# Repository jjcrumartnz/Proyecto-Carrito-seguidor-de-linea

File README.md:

# Proyecto-Carrito-seguidor-de-linea

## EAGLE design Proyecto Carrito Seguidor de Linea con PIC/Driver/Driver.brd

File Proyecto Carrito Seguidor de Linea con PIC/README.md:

# Esquematicos-y-pogramacion-de-robot-seguidor-de-linea

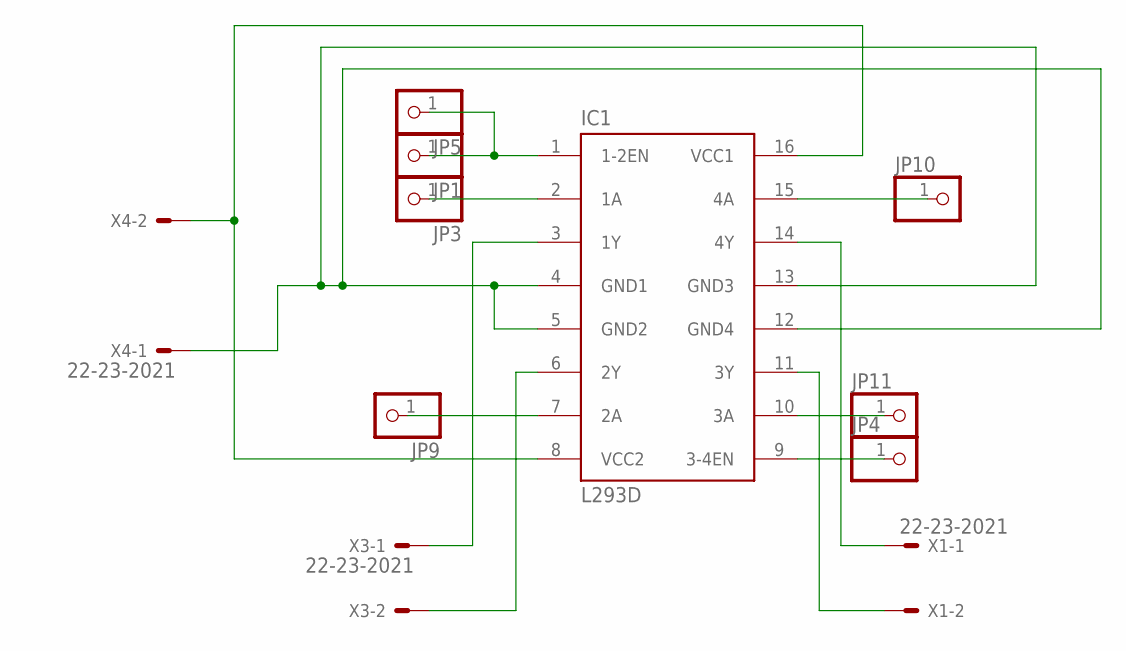
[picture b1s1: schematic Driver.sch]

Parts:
IC1: L293D; DIL16
JP1, JP3, JP4, JP5, JP9, JP10, JP11: PINHD-1X1; 1X01
X1, X3, X4: 22-23-2021

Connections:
unnamed: IC1.14 (4Y), X1.1
unnamed: IC1.1 (1-2EN), JP1.1, JP5.1
unnamed: IC1.2 (1A), JP3.1
unnamed: IC1.7 (2A), JP9.1
unnamed: IC1.10 (3A), JP11.1
unnamed: IC1.11 (3Y), X1.2
unnamed: IC1.3 (1Y), X3.1
unnamed: IC1.6 (2Y), X3.2
unnamed: IC1.15 (4A), JP10.1
unnamed: IC1.4 (GND1), IC1.5 (GND2), IC1.12 (GND4), IC1.13 (GND3), X4.1
unnamed: IC1.8 (VCC2), IC1.16 (VCC1), X4.2
unnamed: IC1.9 (3-4EN), JP4.1

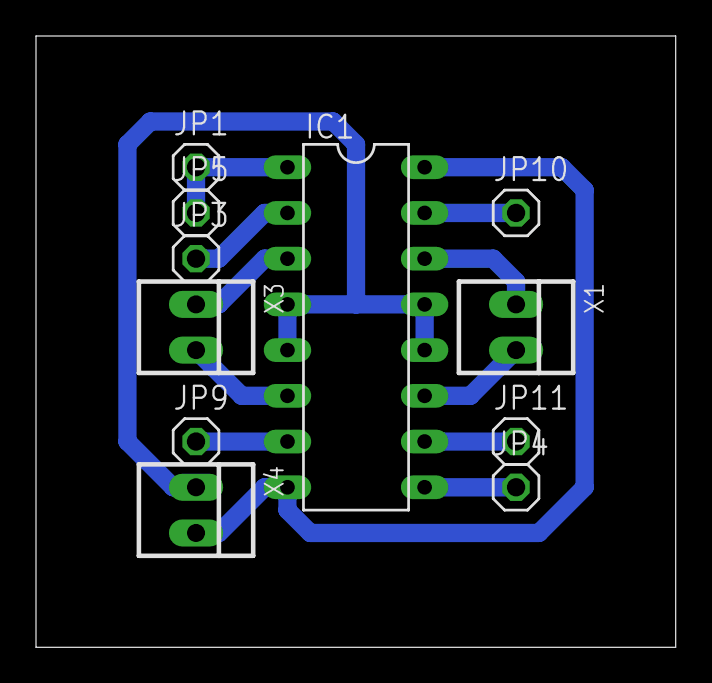
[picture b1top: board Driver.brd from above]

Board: 2 copper layers, 35.5 x 34.0 mm, 11 parts (0 on the bottom side), 12 nets.

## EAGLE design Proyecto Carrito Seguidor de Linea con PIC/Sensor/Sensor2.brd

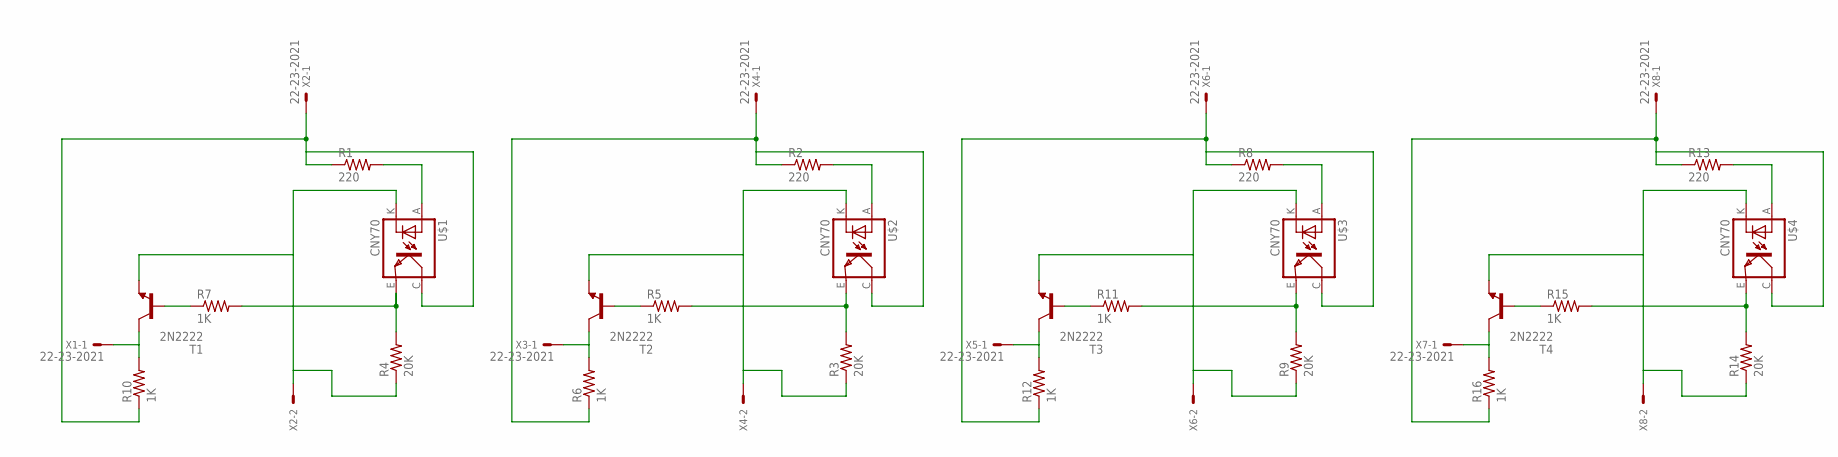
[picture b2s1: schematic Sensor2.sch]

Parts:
R1, R2, R8, R13: 220; 0204/7
R3, R4, R9, R14: 20K; 0204/7
R5, R6, R7, R10, R11, R12, R15, R16: 1K; 0204/7
T1, T2, T3, T4: 2N2222; TO18
U$1, U$2, U$3, U$4: CNY70; 4
X1, X2, X3, X4, X5, X6, X7, X8: 22-23-2021

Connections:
unnamed: R1.2, U$1.A
unnamed: R4.1, T1.1 (E), U$1.K (C), X2.2
unnamed: R2.2, U$2.A
unnamed: R3.1, T2.1 (E), U$2.K (C), X4.2
unnamed: R4.2, R7.2, U$1.E (EMI)
unnamed: R3.2, R5.2, U$2.E (EMI)
unnamed: R10.2, T1.3 (C), X1.1
unnamed: R7.1, T1.2 (B)
unnamed: R6.2, T2.3 (C), X3.1
unnamed: R1.1, R10.1, U$1.C (COL), X2.1
unnamed: R5.1, T2.2 (B)
unnamed: R2.1, R6.1, U$2.C (COL), X4.1
unnamed: R8.2, U$3.A
unnamed: R9.1, T3.1 (E), U$3.K (C), X6.2
unnamed: R9.2, R11.2, U$3.E (EMI)
unnamed: R12.2, T3.3 (C), X5.1
unnamed: R11.1, T3.2 (B)
unnamed: R8.1, R12.1, U$3.C (COL), X6.1
unnamed: R13.2, U$4.A
unnamed: R14.1, T4.1 (E), U$4.K (C), X8.2
unnamed: R14.2, R15.2, U$4.E (EMI)
unnamed: R16.2, T4.3 (C), X7.1
unnamed: R15.1, T4.2 (B)
unnamed: R13.1, R16.1, U$4.C (COL), X8.1

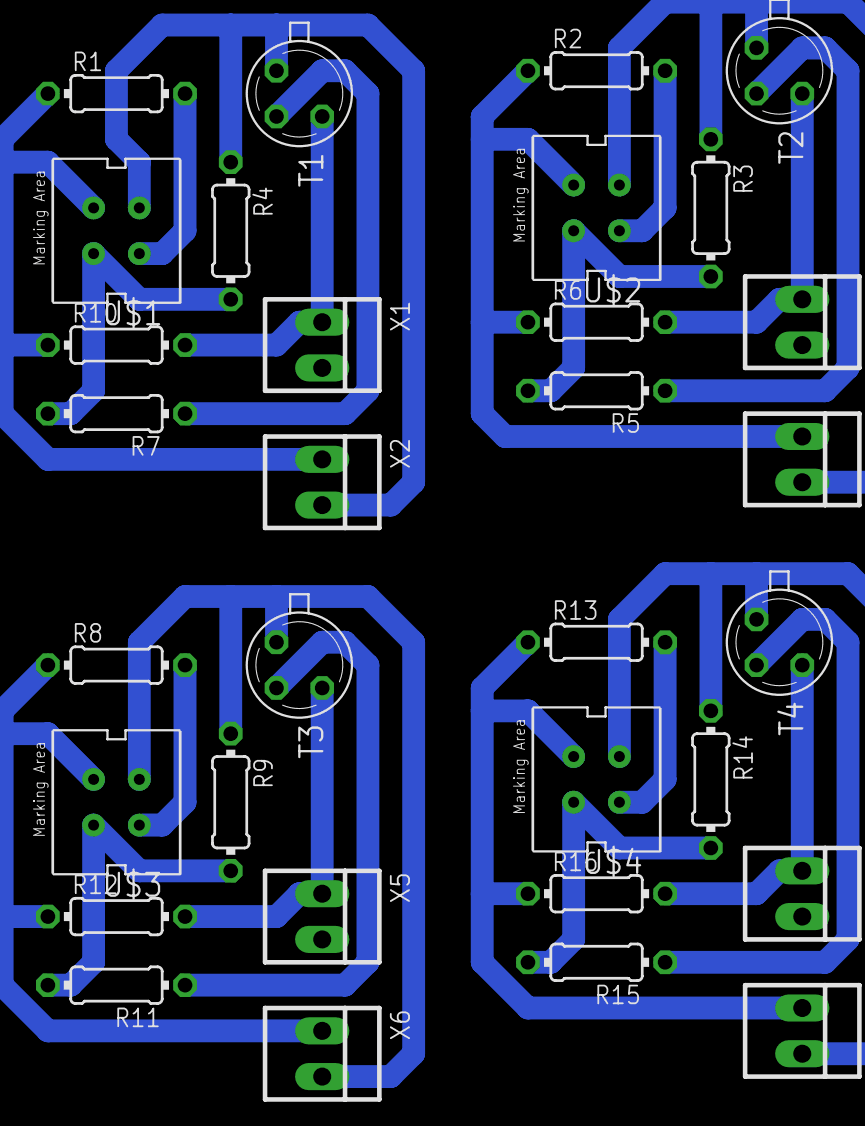
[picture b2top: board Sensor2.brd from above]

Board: 2 copper layers, 32 parts (0 on the bottom side), 24 nets.

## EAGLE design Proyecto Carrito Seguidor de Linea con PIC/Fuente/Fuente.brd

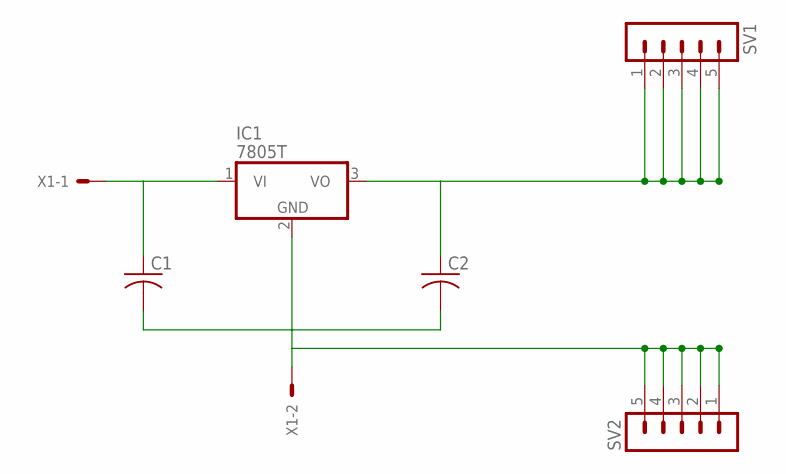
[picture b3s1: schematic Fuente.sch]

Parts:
C1, C2: C-US025-030X050; C025-030X050
IC1: 7805T; TO220H
SV1, SV2: MA05-1
X1: KK-156-2

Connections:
unnamed: C1.1, IC1.1 (VI), X1.1
unnamed: C2.1, IC1.3 (VO), SV1.1, SV1.2, SV1.3, SV1.4, SV1.5
unnamed: C1.2, C2.2, IC1.2 (GND), SV2.1, SV2.2, SV2.3, SV2.4, SV2.5, X1.2

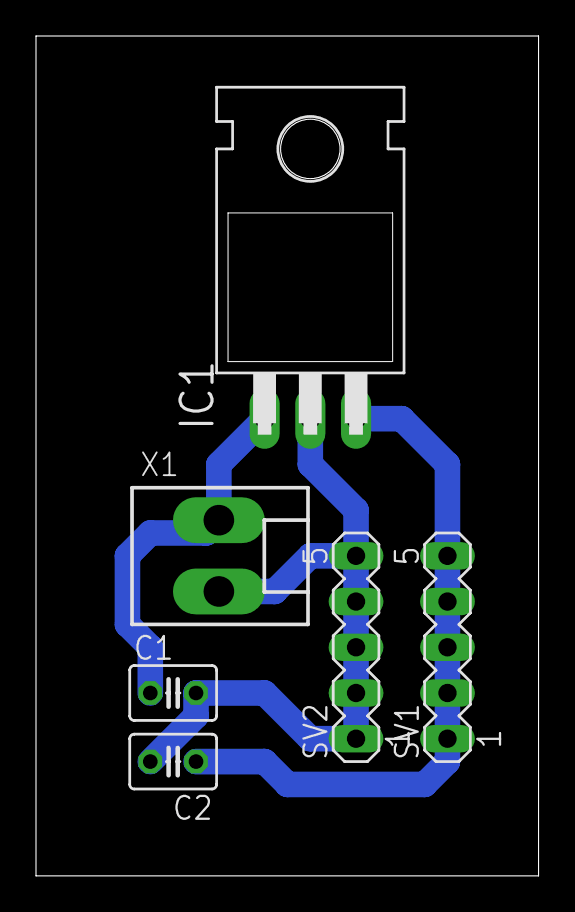
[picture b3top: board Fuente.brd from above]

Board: 2 copper layers, 27.9 x 46.7 mm, 6 parts (0 on the bottom side), 3 nets.
